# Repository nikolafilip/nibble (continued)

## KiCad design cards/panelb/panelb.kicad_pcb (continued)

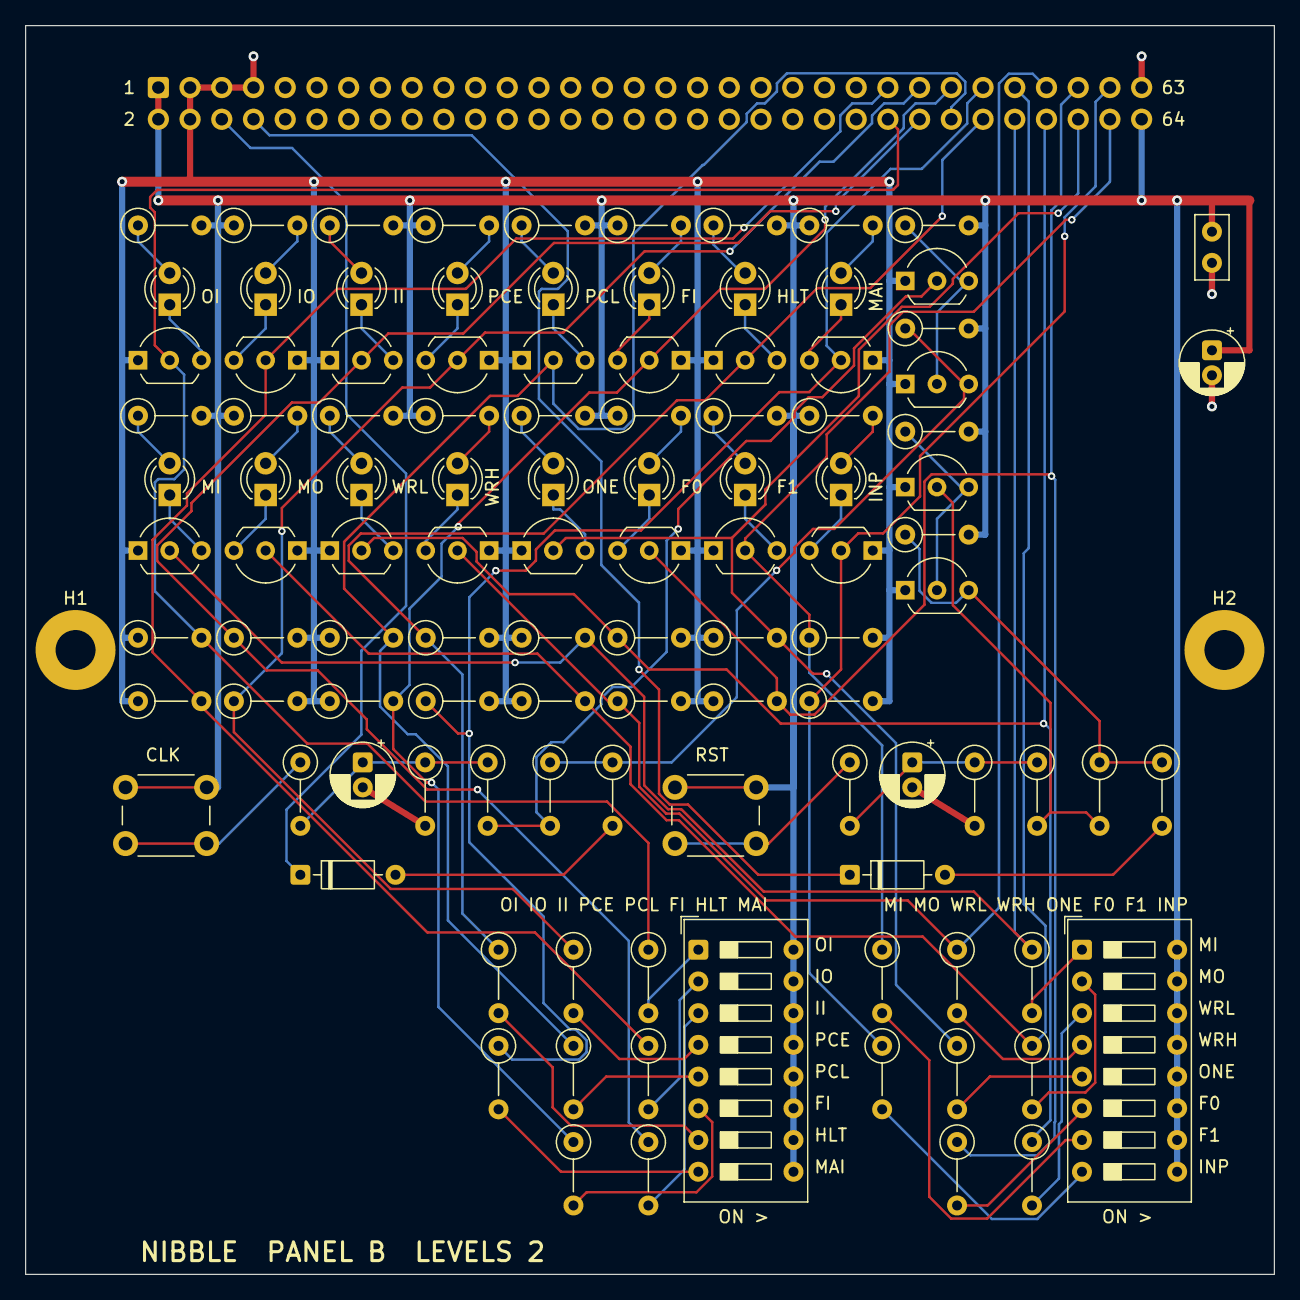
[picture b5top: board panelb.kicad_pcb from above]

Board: 2 copper layers, 100.0 x 100.0 mm, 111 parts (1 on the bottom side), 80 nets.

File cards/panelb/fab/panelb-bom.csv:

"Reference","Value","Footprint","QUANTITY"
"C1","100n","Capacitor_THT:C_Disc_D5.0mm_W2.5mm_P2.50mm","1"
"C2","10u","Capacitor_THT:CP_Radial_D5.0mm_P2.00mm","1"
"C3,C4","1u","Capacitor_THT:CP_Radial_D5.0mm_P2.00mm","2"
"D1-D16","LED","LED_THT:LED_D3.0mm","16"
"D17,D18","1N4148","Diode_THT:D_DO-35_SOD27_P7.62mm_Horizontal","2"
"J1","BUS","Connector_IDC:IDC-Header_2x32_P2.54mm_Vertical","1"
"Q1-Q20","2N7000","Package_TO_SOT_THT:TO-92_Inline_Wide","20"
"R1-R16,R18,R20","1k","Resistor_THT:R_Axial_DIN0207_L6.3mm_D2.5mm_P5.08mm_Vertical","18"
"R17,R19","47k","Resistor_THT:R_Axial_DIN0207_L6.3mm_D2.5mm_P5.08mm_Vertical","2"
"R21-R36,R56,R61","1Meg","Resistor_THT:R_Axial_DIN0207_L6.3mm_D2.5mm_P5.08mm_Vertical","18"
"R37-R53,R58","10k","Resistor_THT:R_Axial_DIN0207_L6.3mm_D2.5mm_P5.08mm_Vertical","18"
"R54,R59","220k","Resistor_THT:R_Axial_DIN0207_L6.3mm_D2.5mm_P5.08mm_Vertical","2"
"R55,R60","100k","Resistor_THT:R_Axial_DIN0207_L6.3mm_D2.5mm_P5.08mm_Vertical","2"
"R57,R62","100","Resistor_THT:R_Axial_DIN0207_L6.3mm_D2.5mm_P5.08mm_Vertical","2"
"SW1","OI IO II PCE PCL FI HLT MAI (switch ON = 1)","Button_Switch_THT:SW_DIP_SPSTx08_Slide_9.78x22.5mm_W7.62mm_P2.54mm","1"
"SW2","MI MO WRL WRH ONE F0 F1 INP","Button_Switch_THT:SW_DIP_SPSTx08_Slide_9.78x22.5mm_W7.62mm_P2.54mm","1"
"SW3","CLK","Button_Switch_THT:SW_PUSH_6mm","1"
"SW4","RST","Button_Switch_THT:SW_PUSH_6mm","1"

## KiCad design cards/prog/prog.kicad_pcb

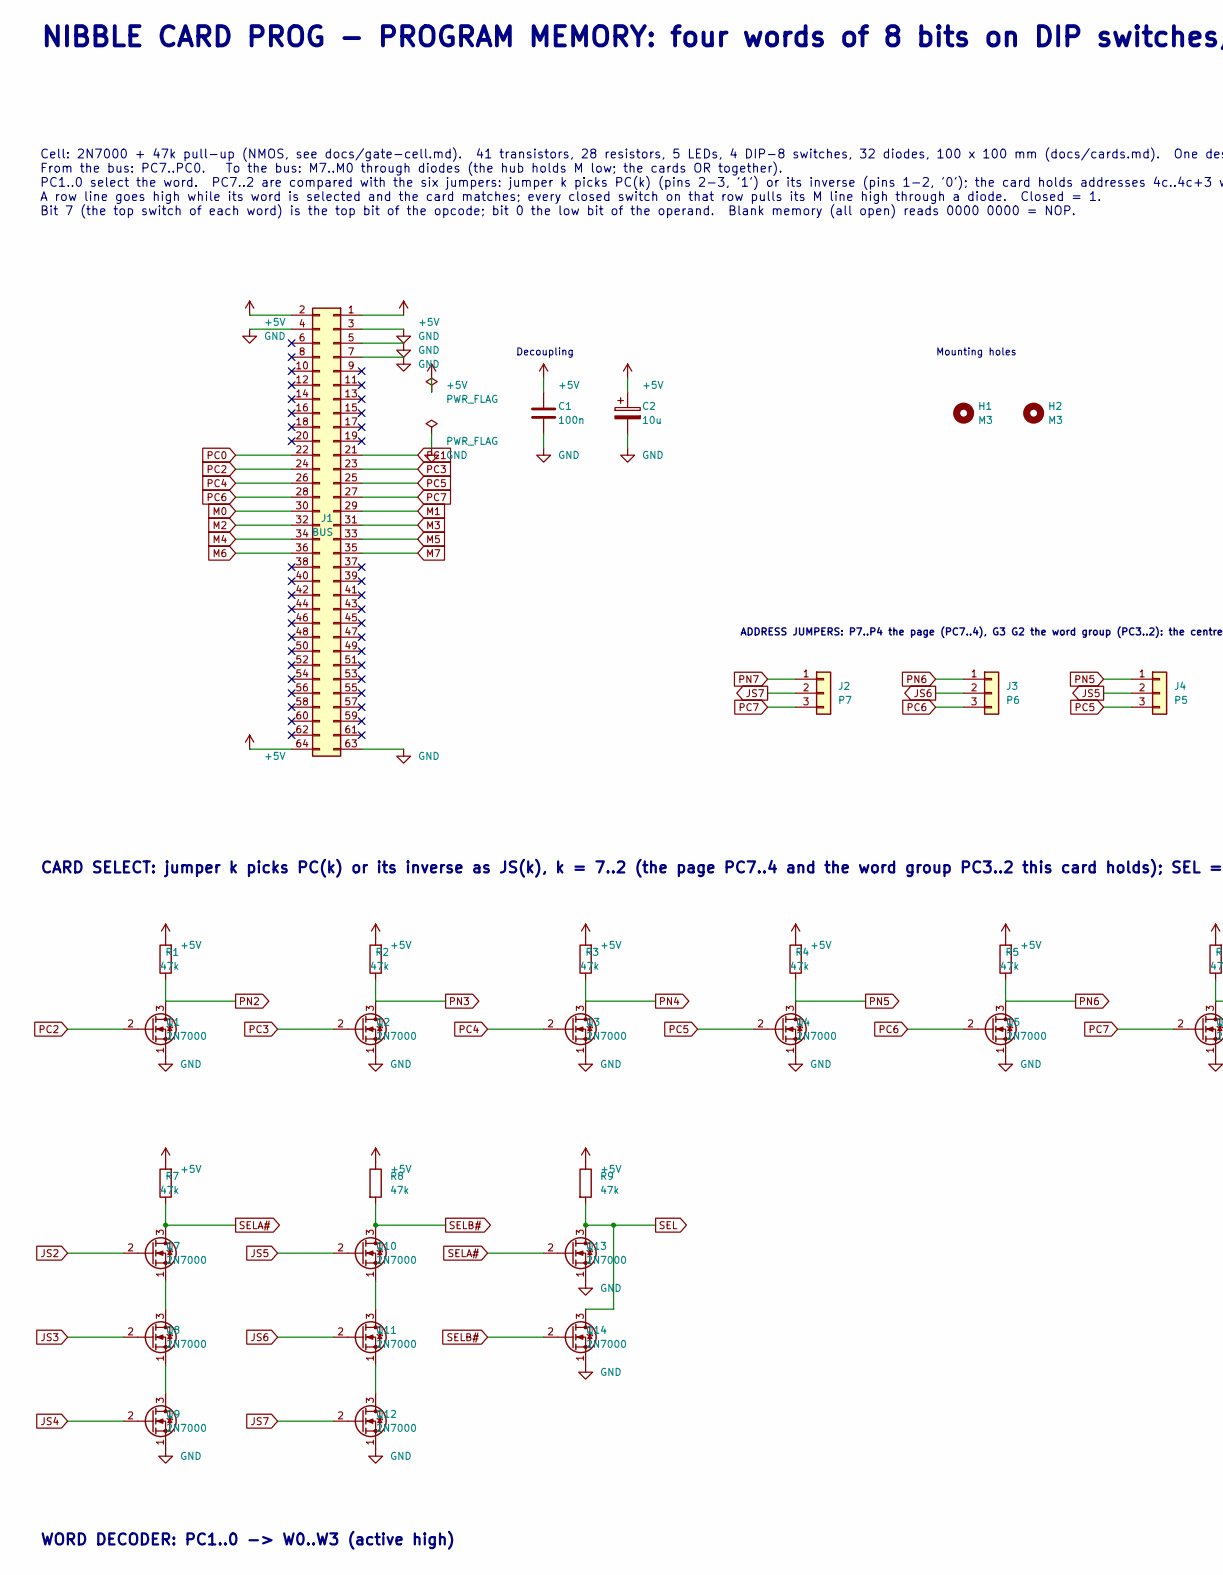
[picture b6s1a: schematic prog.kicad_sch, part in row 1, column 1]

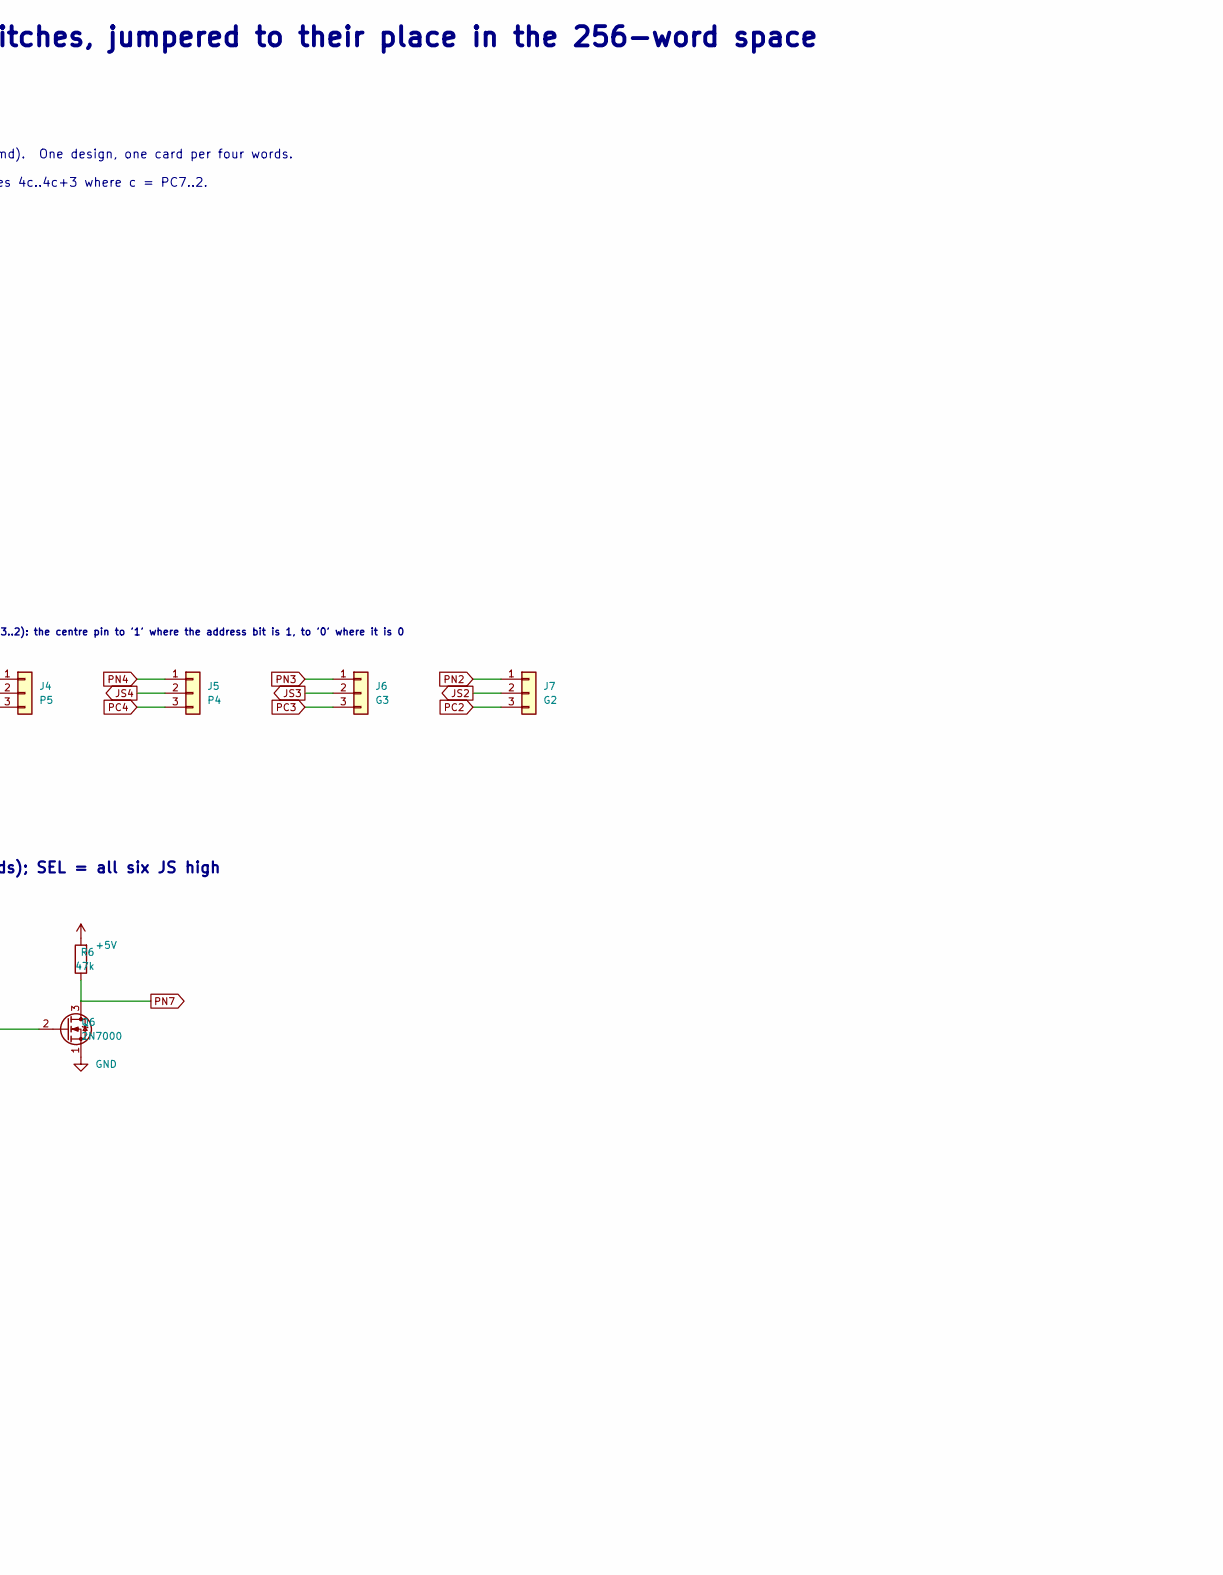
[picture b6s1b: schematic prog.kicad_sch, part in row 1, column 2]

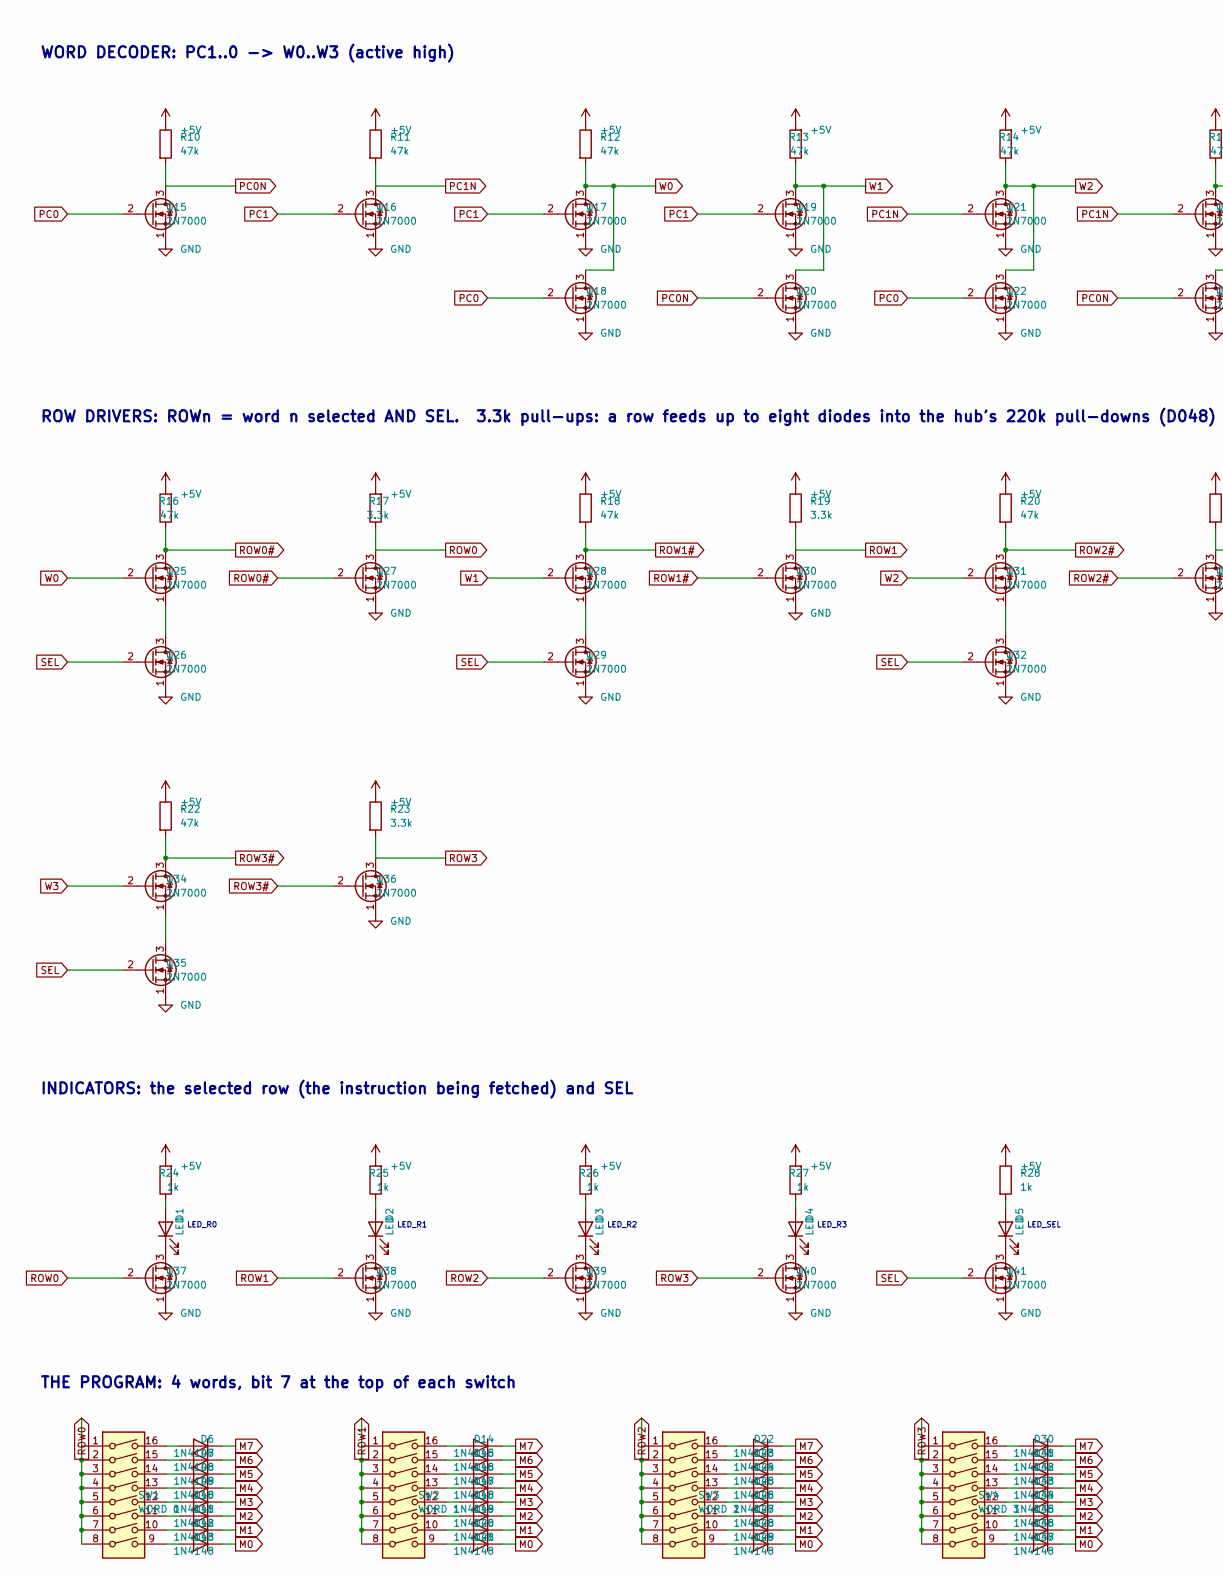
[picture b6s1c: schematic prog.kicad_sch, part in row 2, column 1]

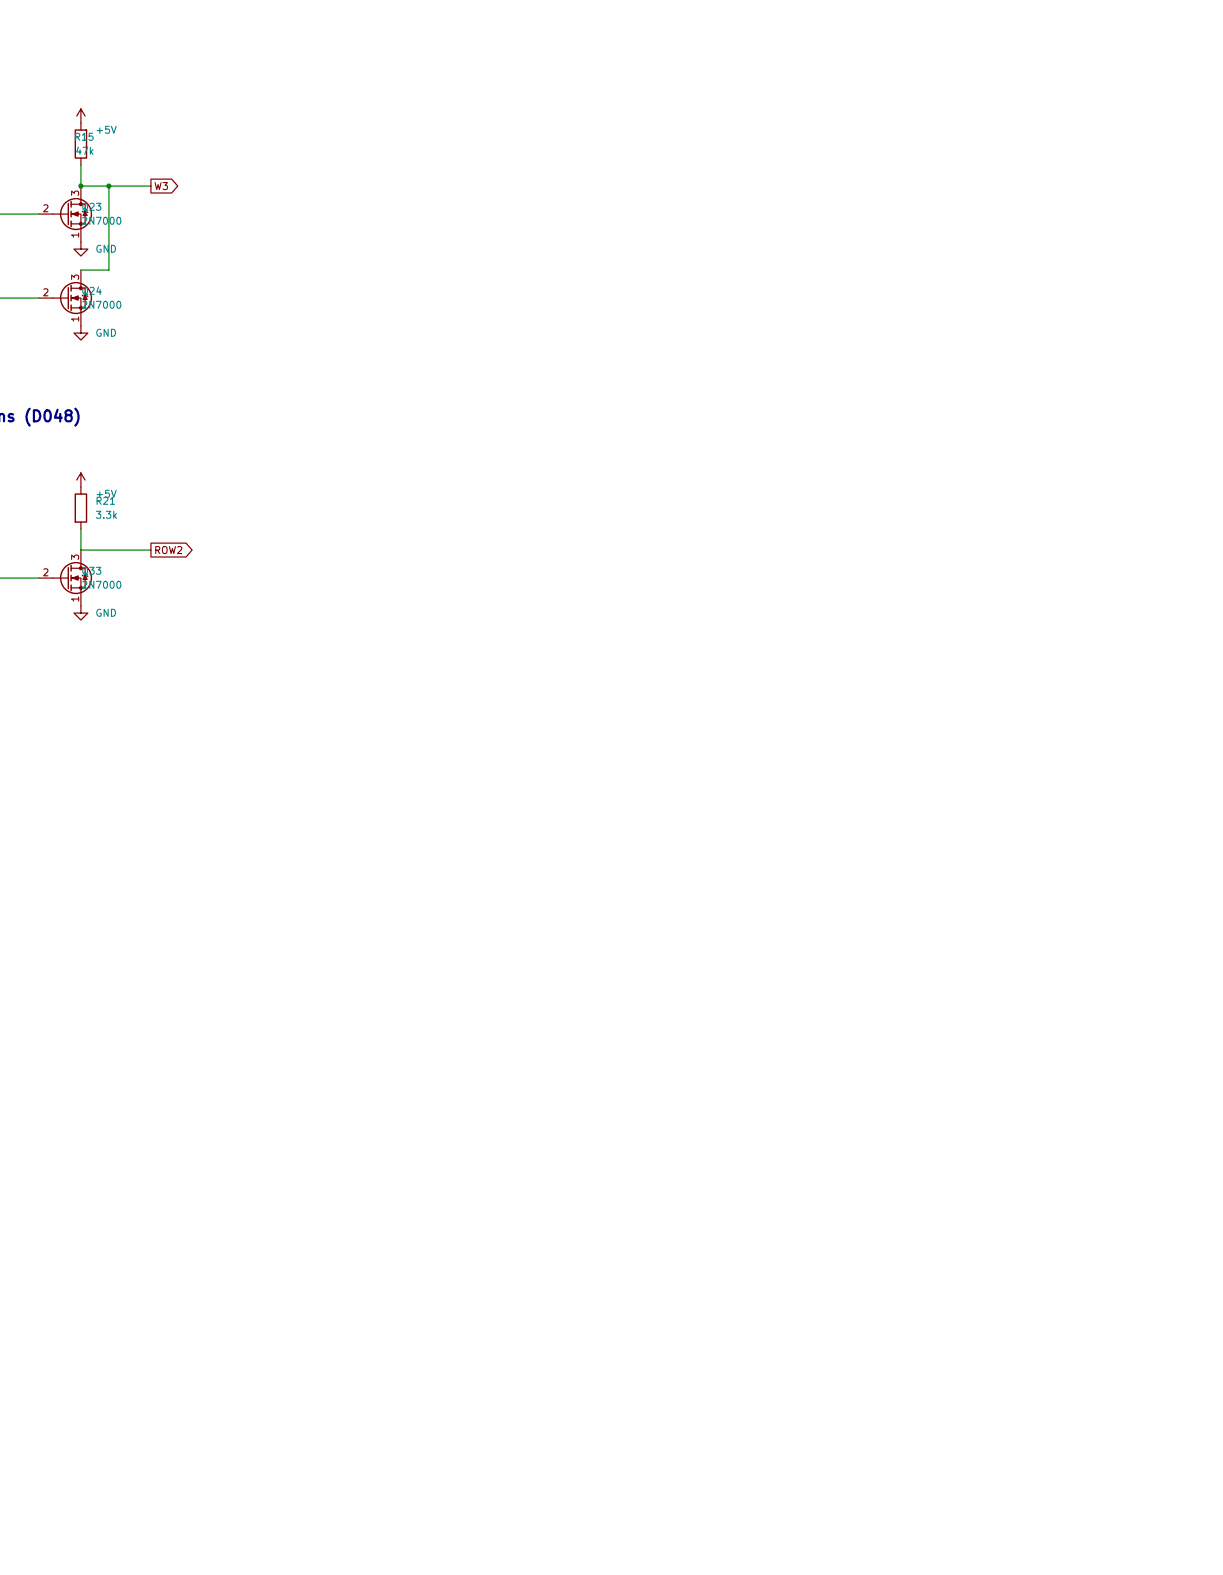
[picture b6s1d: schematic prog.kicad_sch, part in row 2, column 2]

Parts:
C1: 100n; C_Disc_D5.0mm_W2.5mm_P2.50mm
C2: 10u; CP_Radial_D5.0mm_P2.00mm
D1, D2, D3, D4, D5: LED; LED_D3.0mm
D6, D7, D8, D9, D10, D11, D12, D13, D14, D15, D16, D17, D18, D19, D20, D21, D22, D23, D24, D25, D26, D27, D28, D29, D30, D31, D32, D33, D34, D35, D36, D37: 1N4148; D_DO-35_SOD27_P2.54mm_Vertical_AnodeUp
H1, H2: M3; MountingHole_3.2mm_M3_Pad
J1: BUS; IDC-Header_2x32_P2.54mm_Vertical
J2: P7; PinHeader_1x03_P2.54mm_Vertical
J3: P6; PinHeader_1x03_P2.54mm_Vertical
J4: P5; PinHeader_1x03_P2.54mm_Vertical
J5: P4; PinHeader_1x03_P2.54mm_Vertical
J6: G3; PinHeader_1x03_P2.54mm_Vertical
J7: G2; PinHeader_1x03_P2.54mm_Vertical
Q1, Q2, Q3, Q4, Q5, Q6, Q7, Q8, Q9, Q10, Q11, Q12, Q13, Q14, Q15, Q16, Q17, Q18, Q19, Q20, Q21, Q22, Q23, Q24, Q25, Q26, Q27, Q28, Q29, Q30, Q31, Q32, Q33, Q34, Q35, Q36, Q37, Q38, Q39, Q40, Q41: 2N7000; TO-92_Inline_Wide
R1, R2, R3, R4, R5, R6, R7, R8, R9, R10, R11, R12, R13, R14, R15, R16, R18, R20, R22: 47k; R_Axial_DIN0207_L6.3mm_D2.5mm_P5.08mm_Vertical
R17, R19, R21, R23: 3.3k; R_Axial_DIN0207_L6.3mm_D2.5mm_P5.08mm_Vertical
R24, R25, R26, R27, R28: 1k; R_Axial_DIN0207_L6.3mm_D2.5mm_P5.08mm_Vertical
SW1: WORD 0; SW_DIP_SPSTx08_Slide_9.78x22.5mm_W7.62mm_P2.54mm
SW2: WORD 1; SW_DIP_SPSTx08_Slide_9.78x22.5mm_W7.62mm_P2.54mm
SW3: WORD 2; SW_DIP_SPSTx08_Slide_9.78x22.5mm_W7.62mm_P2.54mm
SW4: WORD 3; SW_DIP_SPSTx08_Slide_9.78x22.5mm_W7.62mm_P2.54mm

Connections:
+5V: C1.1, C2.1, J1.1, J1.2, J1.64, R1.2, R2.2, R3.2, R4.2, R5.2, R6.2, R7.2, R8.1, R9.1, R10.1, R11.1, R12.1, R13.2, R14.2, R15.2, R16.2, R17.2, R18.1, R19.1, R20.1, R21.1, R22.1, R23.1, R24.2, R25.2, R26.2, R27.2, R28.1
GND: C1.2, C2.2, J1.3, J1.4, J1.5, J1.7, J1.63, Q1.1 (S), Q2.1 (S), Q3.1 (S), Q4.1 (S), Q5.1 (S), Q6.1 (S), Q9.1 (S), Q12.1 (S), Q13.1 (S), Q14.1 (S), Q15.1 (S), Q16.1 (S), Q17.1 (S), Q18.1 (S), Q19.1 (S), Q20.1 (S), Q21.1 (S), Q22.1 (S), Q23.1 (S), Q24.1 (S), Q26.1 (S), Q27.1 (S), Q29.1 (S), Q30.1 (S), Q32.1 (S), Q33.1 (S), Q35.1 (S), Q36.1 (S), Q37.1 (S), Q38.1 (S), Q39.1 (S), Q40.1 (S), Q41.1 (S)
JS2: J7.2, Q7.2 (G)
JS3: J6.2, Q8.2 (G)
JS4: J5.2, Q9.2 (G)
JS5: J4.2, Q10.2 (G)
JS6: J3.2, Q11.2 (G)
JS7: J2.2, Q12.2 (G)
M0: D13.1 (K), D21.1 (K), D29.1 (K), D37.1 (K), J1.30
M1: D12.1 (K), D20.1 (K), D28.1 (K), D36.1 (K), J1.29
M2: D11.1 (K), D19.1 (K), D27.1 (K), D35.1 (K), J1.32
M3: D10.1 (K), D18.1 (K), D26.1 (K), D34.1 (K), J1.31
M4: D9.1 (K), D17.1 (K), D25.1 (K), D33.1 (K), J1.34
M5: D8.1 (K), D16.1 (K), D24.1 (K), D32.1 (K), J1.33
M6: D7.1 (K), D15.1 (K), D23.1 (K), D31.1 (K), J1.36
M7: D6.1 (K), D14.1 (K), D22.1 (K), D30.1 (K), J1.35
unnamed: D1.2 (A), R24.1
unnamed: D1.1 (K), Q37.3 (D)
unnamed: D2.2 (A), R25.1
unnamed: D2.1 (K), Q38.3 (D)
unnamed: D3.2 (A), R26.1
unnamed: D3.1 (K), Q39.3 (D)
unnamed: D4.2 (A), R27.1
unnamed: D4.1 (K), Q40.3 (D)
unnamed: D5.2 (A), R28.2
unnamed: D5.1 (K), Q41.3 (D)
unnamed: D6.2 (A), SW1.16
unnamed: D7.2 (A), SW1.15
unnamed: D8.2 (A), SW1.14
unnamed: D9.2 (A), SW1.13
unnamed: D10.2 (A), SW1.12
unnamed: D11.2 (A), SW1.11
unnamed: D12.2 (A), SW1.10
unnamed: D13.2 (A), SW1.9
unnamed: D14.2 (A), SW2.16
unnamed: D15.2 (A), SW2.15
unnamed: D16.2 (A), SW2.14
unnamed: D17.2 (A), SW2.13
unnamed: D18.2 (A), SW2.12
unnamed: D19.2 (A), SW2.11
unnamed: D20.2 (A), SW2.10
unnamed: D21.2 (A), SW2.9
unnamed: D22.2 (A), SW3.16
unnamed: D23.2 (A), SW3.15
unnamed: D24.2 (A), SW3.14
unnamed: D25.2 (A), SW3.13
unnamed: D26.2 (A), SW3.12
unnamed: D27.2 (A), SW3.11
unnamed: D28.2 (A), SW3.10
unnamed: D29.2 (A), SW3.9
unnamed: D30.2 (A), SW4.16
unnamed: D31.2 (A), SW4.15
unnamed: D32.2 (A), SW4.14
unnamed: D33.2 (A), SW4.13
unnamed: D34.2 (A), SW4.12
unnamed: D35.2 (A), SW4.11
unnamed: D36.2 (A), SW4.10
unnamed: D37.2 (A), SW4.9
unnamed: Q7.1 (S), Q8.3 (D)
unnamed: Q8.1 (S), Q9.3 (D)
unnamed: Q10.1 (S), Q11.3 (D)
unnamed: Q11.1 (S), Q12.3 (D)
unnamed: Q25.1 (S), Q26.3 (D)
unnamed: Q28.1 (S), Q29.3 (D)
unnamed: Q31.1 (S), Q32.3 (D)
unnamed: Q34.1 (S), Q35.3 (D)
PC0: J1.22, Q15.2 (G), Q18.2 (G), Q22.2 (G)
PC0N: Q15.3 (D), Q20.2 (G), Q24.2 (G), R10.2
PC1: J1.21, Q16.2 (G), Q17.2 (G), Q19.2 (G)
PC1N: Q16.3 (D), Q21.2 (G), Q23.2 (G), R11.2
PC2: J1.24, J7.3, Q1.2 (G)
PC3: J1.23, J6.3, Q2.2 (G)
PC4: J1.26, J5.3, Q3.2 (G)
PC5: J1.25, J4.3, Q4.2 (G)
PC6: J1.28, J3.3, Q5.2 (G)
PC7: J1.27, J2.3, Q6.2 (G)
PN2: J7.1, Q1.3 (D), R1.1
PN3: J6.1, Q2.3 (D), R2.1
PN4: J5.1, Q3.3 (D), R3.1
PN5: J4.1, Q4.3 (D), R4.1
PN6: J3.1, Q5.3 (D), R5.1
PN7: J2.1, Q6.3 (D), R6.1
ROW0: Q27.3 (D), Q37.2 (G), R17.1, SW1.1, SW1.2, SW1.3, SW1.4, SW1.5, SW1.6, SW1.7, SW1.8
ROW0#: Q25.3 (D), Q27.2 (G), R16.1
ROW1: Q30.3 (D), Q38.2 (G), R19.2, SW2.1, SW2.2, SW2.3, SW2.4, SW2.5, SW2.6, SW2.7, SW2.8
ROW1#: Q28.3 (D), Q30.2 (G), R18.2
ROW2: Q33.3 (D), Q39.2 (G), R21.2, SW3.1, SW3.2, SW3.3, SW3.4, SW3.5, SW3.6, SW3.7, SW3.8
ROW2#: Q31.3 (D), Q33.2 (G), R20.2
ROW3: Q36.3 (D), Q40.2 (G), R23.2, SW4.1, SW4.2, SW4.3, SW4.4, SW4.5, SW4.6, SW4.7, SW4.8
ROW3#: Q34.3 (D), Q36.2 (G), R22.2
SEL: Q13.3 (D), Q14.3 (D), Q26.2 (G), Q29.2 (G), Q32.2 (G), Q35.2 (G), Q41.2 (G), R9.2
SELA#: Q7.3 (D), Q13.2 (G), R7.1
SELB#: Q10.3 (D), Q14.2 (G), R8.2
W0: Q17.3 (D), Q18.3 (D), Q25.2 (G), R12.2
W1: Q19.3 (D), Q20.3 (D), Q28.2 (G), R13.1
W2: Q21.3 (D), Q22.3 (D), Q31.2 (G), R14.1
W3: Q23.3 (D), Q24.3 (D), Q34.2 (G), R15.1

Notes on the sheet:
NIBBLE CARD PROG - PROGRAM MEMORY: four words of 8 bits on DIP switches, jumpered to their place in the 256-word space
Cell: 2N7000 + 47k pull-up (NMOS, see docs/gate-cell.md). 41 transistors, 28 resistors, 5 LEDs, 4 DIP-8 switches, 32 diodes, 100 x 100 mm (docs/cards.md). One design, one card per four words. From the bus: PC7..PC0. To the bus: M7..M0 through diodes (the hub holds M low; the cards OR together). PC1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
CARD SELECT: jumper k picks PC(k) or its inverse as JS(k), k = 7..2 (the page PC7..4 and the word group PC3..2 this card holds); SEL = all six JS high
WORD DECODER: PC1..0 -> W0..W3 (active high)
ROW DRIVERS: ROWn = word n selected AND SEL. 3.3k pull-ups: a row feeds up to eight diodes into the hub's 220k pull-downs (D048)
INDICATORS: the selected row (the instruction being fetched) and SEL
LED_R0
LED_R1
LED_R2
LED_R3
LED_SEL
Decoupling
Mounting holes
ADDRESS JUMPERS: P7..P4 the page (PC7..4), G3 G2 the word group (PC3..2): the centre pin to '1' where the address bit is 1, to '0' where it is 0
THE PROGRAM: 4 words, bit 7 at the top of each switch

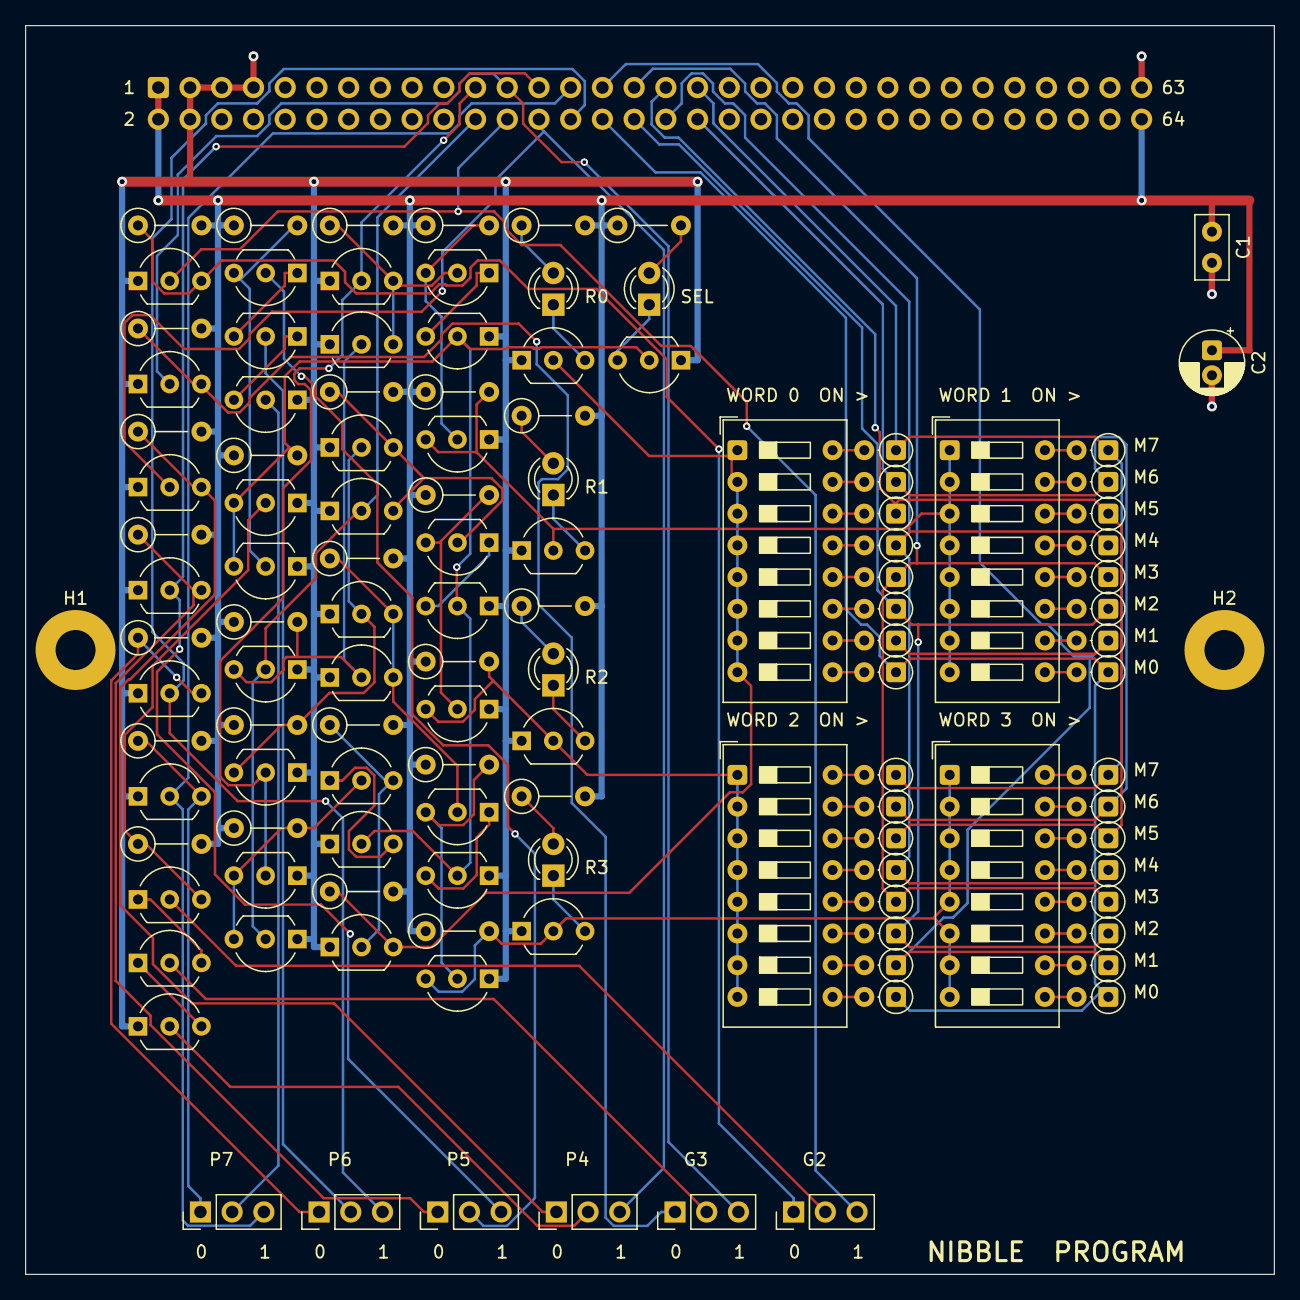
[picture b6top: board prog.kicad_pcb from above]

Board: 2 copper layers, 100.0 x 100.0 mm, 121 parts (1 on the bottom side), 97 nets.

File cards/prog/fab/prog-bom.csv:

"Reference","Value","Footprint","QUANTITY"
"C1","100n","Capacitor_THT:C_Disc_D5.0mm_W2.5mm_P2.50mm","1"
"C2","10u","Capacitor_THT:CP_Radial_D5.0mm_P2.00mm","1"
"D1-D5","LED","LED_THT:LED_D3.0mm","5"
"D6-D37","1N4148","Diode_THT:D_DO-35_SOD27_P2.54mm_Vertical_AnodeUp","32"
"J1","BUS","Connector_IDC:IDC-Header_2x32_P2.54mm_Vertical","1"
"J2","P7","Connector_PinHeader_2.54mm:PinHeader_1x03_P2.54mm_Vertical","1"
"J3","P6","Connector_PinHeader_2.54mm:PinHeader_1x03_P2.54mm_Vertical","1"
"J4","P5","Connector_PinHeader_2.54mm:PinHeader_1x03_P2.54mm_Vertical","1"
"J5","P4","Connector_PinHeader_2.54mm:PinHeader_1x03_P2.54mm_Vertical","1"
"J6","G3","Connector_PinHeader_2.54mm:PinHeader_1x03_P2.54mm_Vertical","1"
"J7","G2","Connector_PinHeader_2.54mm:PinHeader_1x03_P2.54mm_Vertical","1"
"Q1-Q41","2N7000","Package_TO_SOT_THT:TO-92_Inline_Wide","41"
"R1-R16,R18,R20,R22","47k","Resistor_THT:R_Axial_DIN0207_L6.3mm_D2.5mm_P5.08mm_Vertical","19"
"R17,R19,R21,R23","3.3k","Resistor_THT:R_Axial_DIN0207_L6.3mm_D2.5mm_P5.08mm_Vertical","4"
"R24-R28","1k","Resistor_THT:R_Axial_DIN0207_L6.3mm_D2.5mm_P5.08mm_Vertical","5"
"SW1","WORD 0","Button_Switch_THT:SW_DIP_SPSTx08_Slide_9.78x22.5mm_W7.62mm_P2.54mm","1"
"SW2","WORD 1","Button_Switch_THT:SW_DIP_SPSTx08_Slide_9.78x22.5mm_W7.62mm_P2.54mm","1"
"SW3","WORD 2","Button_Switch_THT:SW_DIP_SPSTx08_Slide_9.78x22.5mm_W7.62mm_P2.54mm","1"
"SW4","WORD 3","Button_Switch_THT:SW_DIP_SPSTx08_Slide_9.78x22.5mm_W7.62mm_P2.54mm","1"
